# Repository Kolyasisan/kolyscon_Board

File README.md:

# kolyscon_Board
KiCad files for kolyscon_Board - a PCB for rhythm game controllers

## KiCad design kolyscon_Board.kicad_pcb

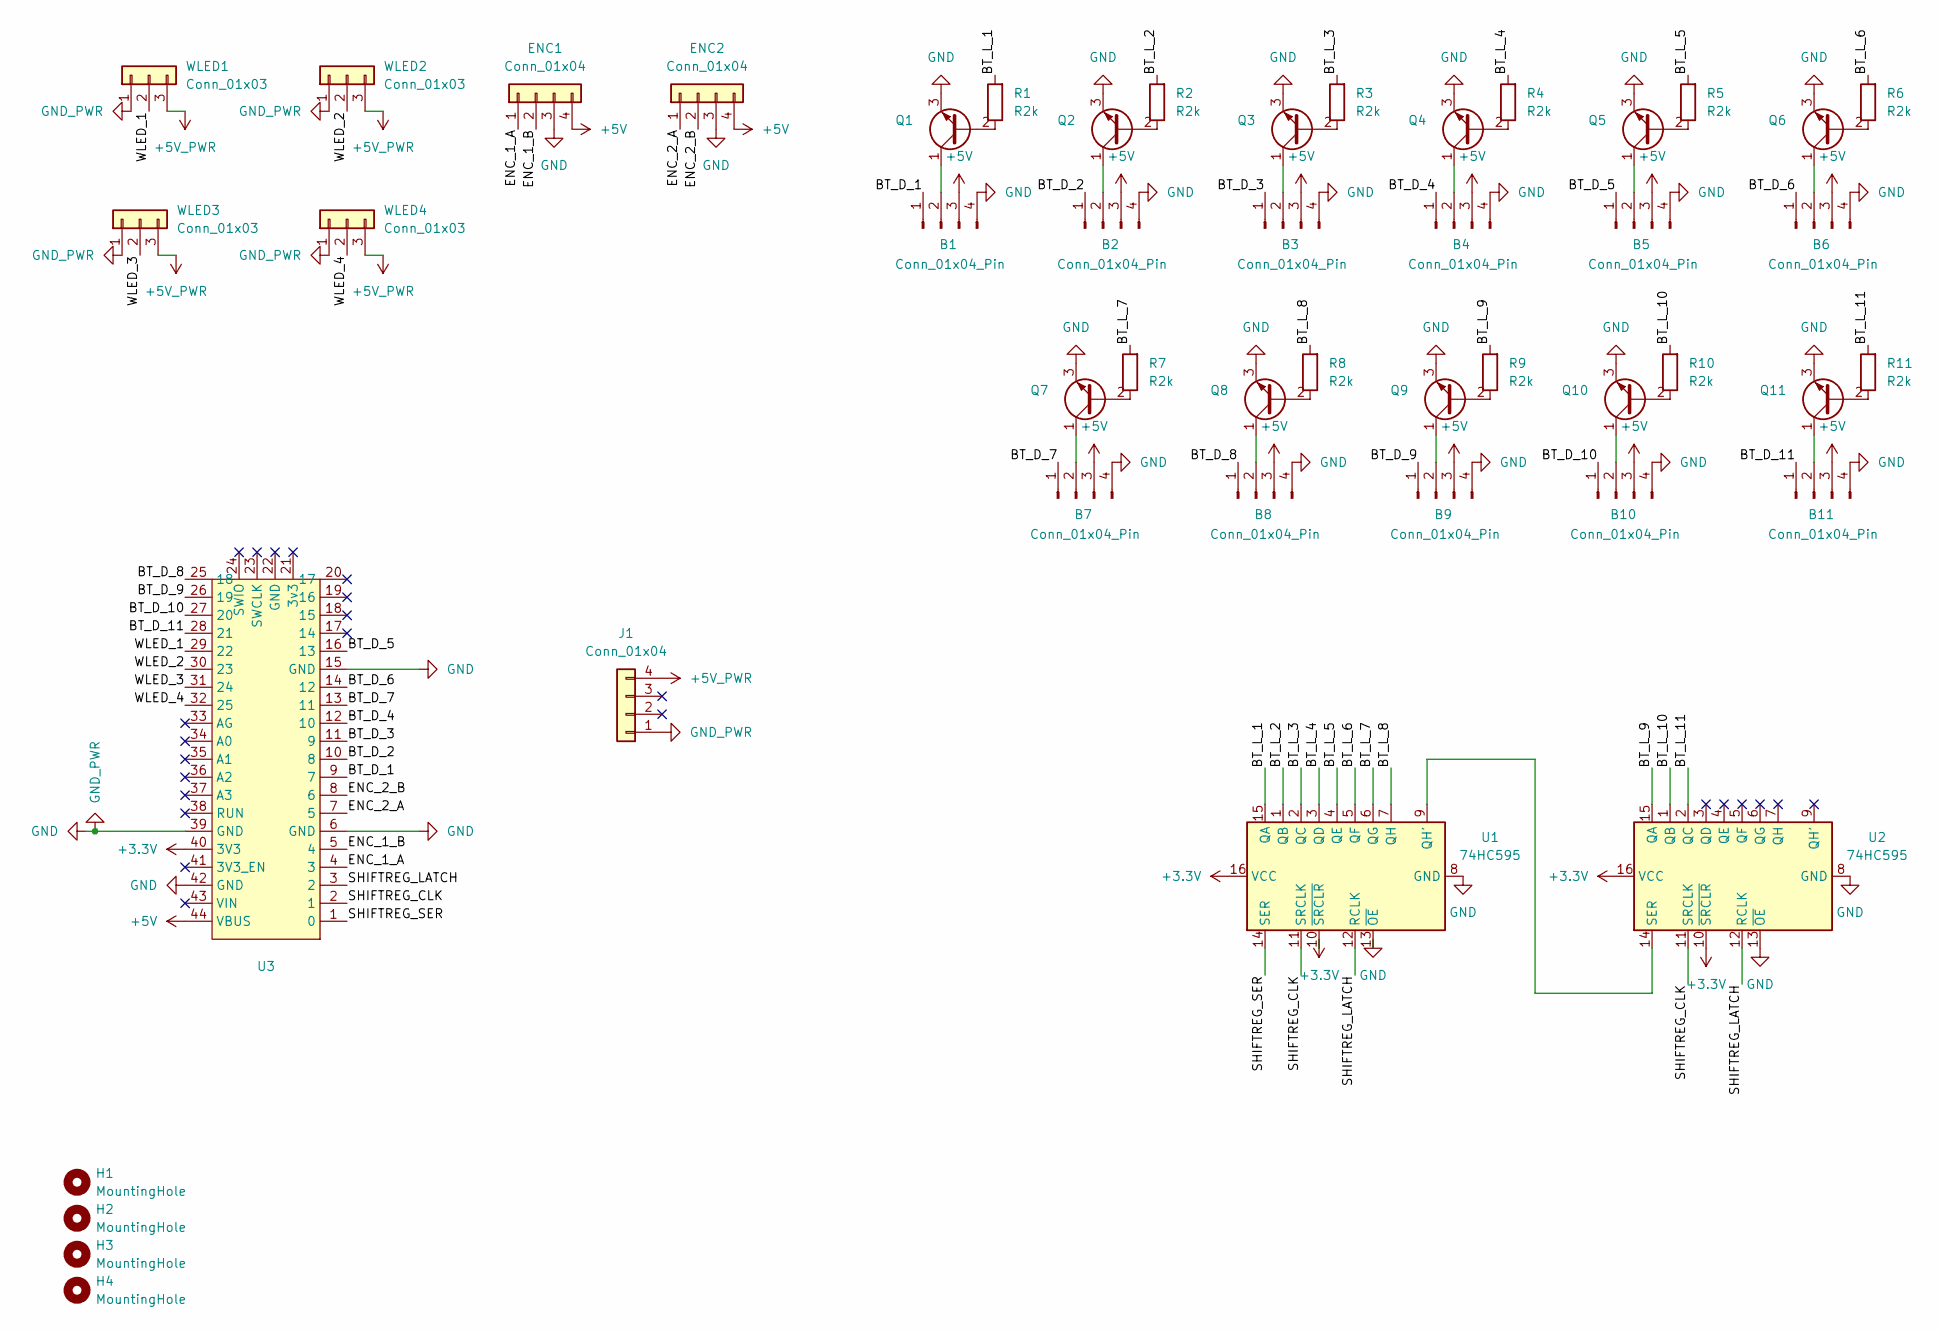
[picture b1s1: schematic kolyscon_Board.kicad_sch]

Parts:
B1, B2, B3, B4, B5, B6, B7, B8, B9, B10, B11: Conn_01x04_Pin; JST_XH_B4B-XH-A_1x04_P2.50mm_Vertical
ENC1, ENC2: Conn_01x04; JST_XH_B4B-XH-A_1x04_P2.50mm_Vertical
H1, H2, H3, H4: MountingHole; MountingHole_3.2mm_M3
J1: Conn_01x04; USB-C_Conn_Small
Q1, Q2, Q3, Q4, Q5, Q6, Q7, Q8, Q9, Q10, Q11: TO-92_Inline
R1, R2, R3, R4, R5, R6, R7, R8, R9, R10, R11: R2k; R_Axial_DIN0204_L3.6mm_D1.6mm_P1.90mm_Vertical
U1, U2: 74HC595; DIP-16_W7.62mm
U3: WeirdPurpleRP2040Board
WLED1, WLED2, WLED3, WLED4: Conn_01x03; JST_XH_B3B-XH-A_1x03_P2.50mm_Vertical

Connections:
+3.3V: U1.10 (~SRCLR), U1.16 (VCC), U2.10 (~SRCLR), U2.16 (VCC), U3.40 (3V3)
+5V: B1.3, B2.3, B3.3, B4.3, B5.3, B6.3, B7.3, B8.3, B9.3, B10.3, B11.3, ENC1.4, ENC2.4, U3.44 (VBUS)
+5V_PWR: J1.4, WLED1.3, WLED2.3, WLED3.3, WLED4.3
/BT_D_1: B1.1, U3.9 (7)
/BT_D_2: B2.1, U3.10 (8)
/BT_D_3: B3.1, U3.11 (9)
/BT_D_4: B4.1, U3.12 (10)
/BT_D_5: B5.1, U3.16 (13)
/BT_D_6: B6.1, U3.14 (12)
/BT_D_7: B7.1, U3.13 (11)
/BT_D_8: B8.1, U3.25 (18)
/BT_D_9: B9.1, U3.26 (19)
/BT_D_10: B10.1, U3.27 (20)
/BT_D_11: B11.1, U3.28 (21)
/BT_L_1: R1.2, U1.15 (QA)
/BT_L_2: R2.2, U1.1 (QB)
/BT_L_3: R3.2, U1.2 (QC)
/BT_L_4: R4.2, U1.3 (QD)
/BT_L_5: R5.2, U1.4 (QE)
/BT_L_6: R6.2, U1.5 (QF)
/BT_L_7: R7.2, U1.6 (QG)
/BT_L_8: R8.2, U1.7 (QH)
/BT_L_9: R9.2, U2.15 (QA)
/BT_L_10: R10.2, U2.1 (QB)
/BT_L_11: R11.2, U2.2 (QC)
/ENC_1_A: ENC1.1, U3.4 (3)
/ENC_1_B: ENC1.2, U3.5 (4)
/ENC_2_A: ENC2.1, U3.7 (5)
/ENC_2_B: ENC2.2, U3.8 (6)
/SHIFTREG_CLK: U1.11 (SRCLK), U2.11 (SRCLK), U3.2 (1)
/SHIFTREG_LATCH: U1.12 (RCLK), U2.12 (RCLK), U3.3 (2)
/SHIFTREG_SER: U1.14 (SER), U3.1 (0)
/WLED_1: U3.29 (22), WLED1.2
/WLED_2: U3.30 (23), WLED2.2
/WLED_3: U3.31 (24), WLED3.2
/WLED_4: U3.32 (25), WLED4.2
GND: B1.4, B2.4, B3.4, B4.4, B5.4, B6.4, B7.4, B8.4, B9.4, B10.4, B11.4, ENC1.3, ENC2.3, J1.1, Q1.3 (E), Q2.3 (E), Q3.3 (E), Q4.3 (E), Q5.3 (E), Q6.3 (E), Q7.3 (E), Q8.3 (E), Q9.3 (E), Q10.3 (E), Q11.3 (E), U1.8 (GND), U1.13 (~OE), U2.8 (GND), U2.13 (~OE), U3.6 (GND), U3.15 (GND), U3.39 (GND), U3.42 (GND), WLED1.1, WLED2.1, WLED3.1, WLED4.1
unnamed: B1.2, Q1.1 (C)
unnamed: B2.2, Q2.1 (C)
unnamed: B3.2, Q3.1 (C)
unnamed: B4.2, Q4.1 (C)
unnamed: B5.2, Q5.1 (C)
unnamed: B6.2, Q6.1 (C)
unnamed: B7.2, Q7.1 (C)
unnamed: B8.2, Q8.1 (C)
unnamed: B9.2, Q9.1 (C)
unnamed: B10.2, Q10.1 (C)
unnamed: B11.2, Q11.1 (C)
unnamed: Q1.2 (B), R1.1
unnamed: Q2.2 (B), R2.1
unnamed: Q3.2 (B), R3.1
unnamed: Q4.2 (B), R4.1
unnamed: Q5.2 (B), R5.1
unnamed: Q6.2 (B), R6.1
unnamed: Q7.2 (B), R7.1
unnamed: Q8.2 (B), R8.1
unnamed: Q9.2 (B), R9.1
unnamed: Q10.2 (B), R10.1
unnamed: Q11.2 (B), R11.1
unnamed: U1.9 (QH'), U2.14 (SER)

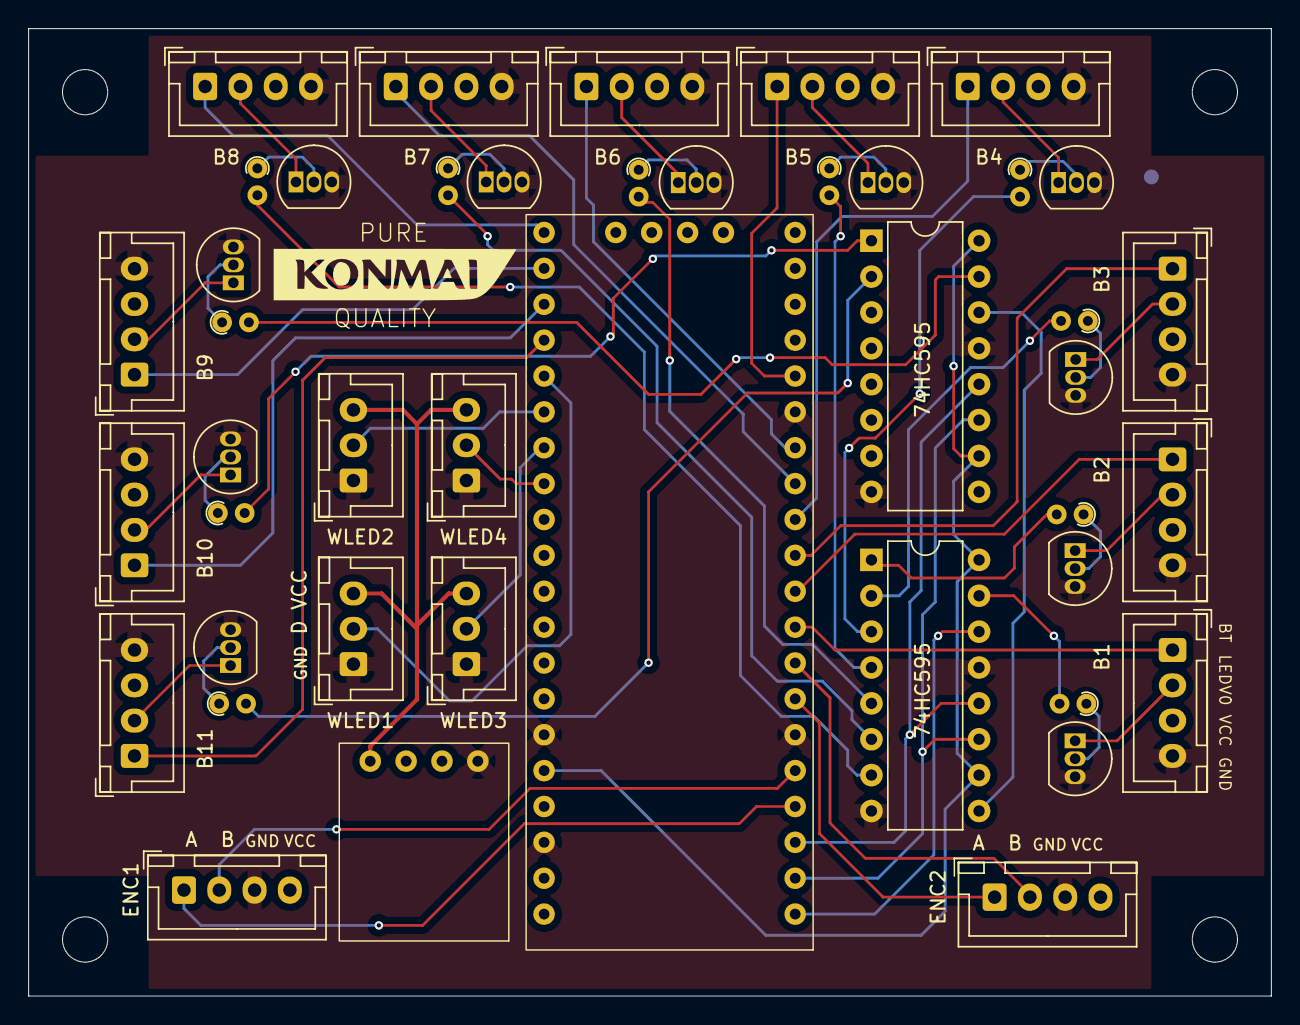
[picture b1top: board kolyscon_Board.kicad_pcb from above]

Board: 2 copper layers, 88.0 x 68.5 mm, 47 parts (0 on the bottom side), 60 nets.

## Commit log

2025-01-27 -Initial commit
2025-01-27 Symbols
2025-01-27 Schematics changes
2025-01-29 Some schema work
2025-01-30 Schema work
2025-02-05 -Routing
2025-02-05 Routing refactors
2025-02-05 V1 finalization
2025-03-06 Some refactors and fixes
2025-03-07 Board refactors and fixes
2025-03-07 Small update
2025-03-07 Trace cleanups
2025-03-07 Small text changes
2025-03-07 1.2 version bump -Slightly better 5v and gnd planes
